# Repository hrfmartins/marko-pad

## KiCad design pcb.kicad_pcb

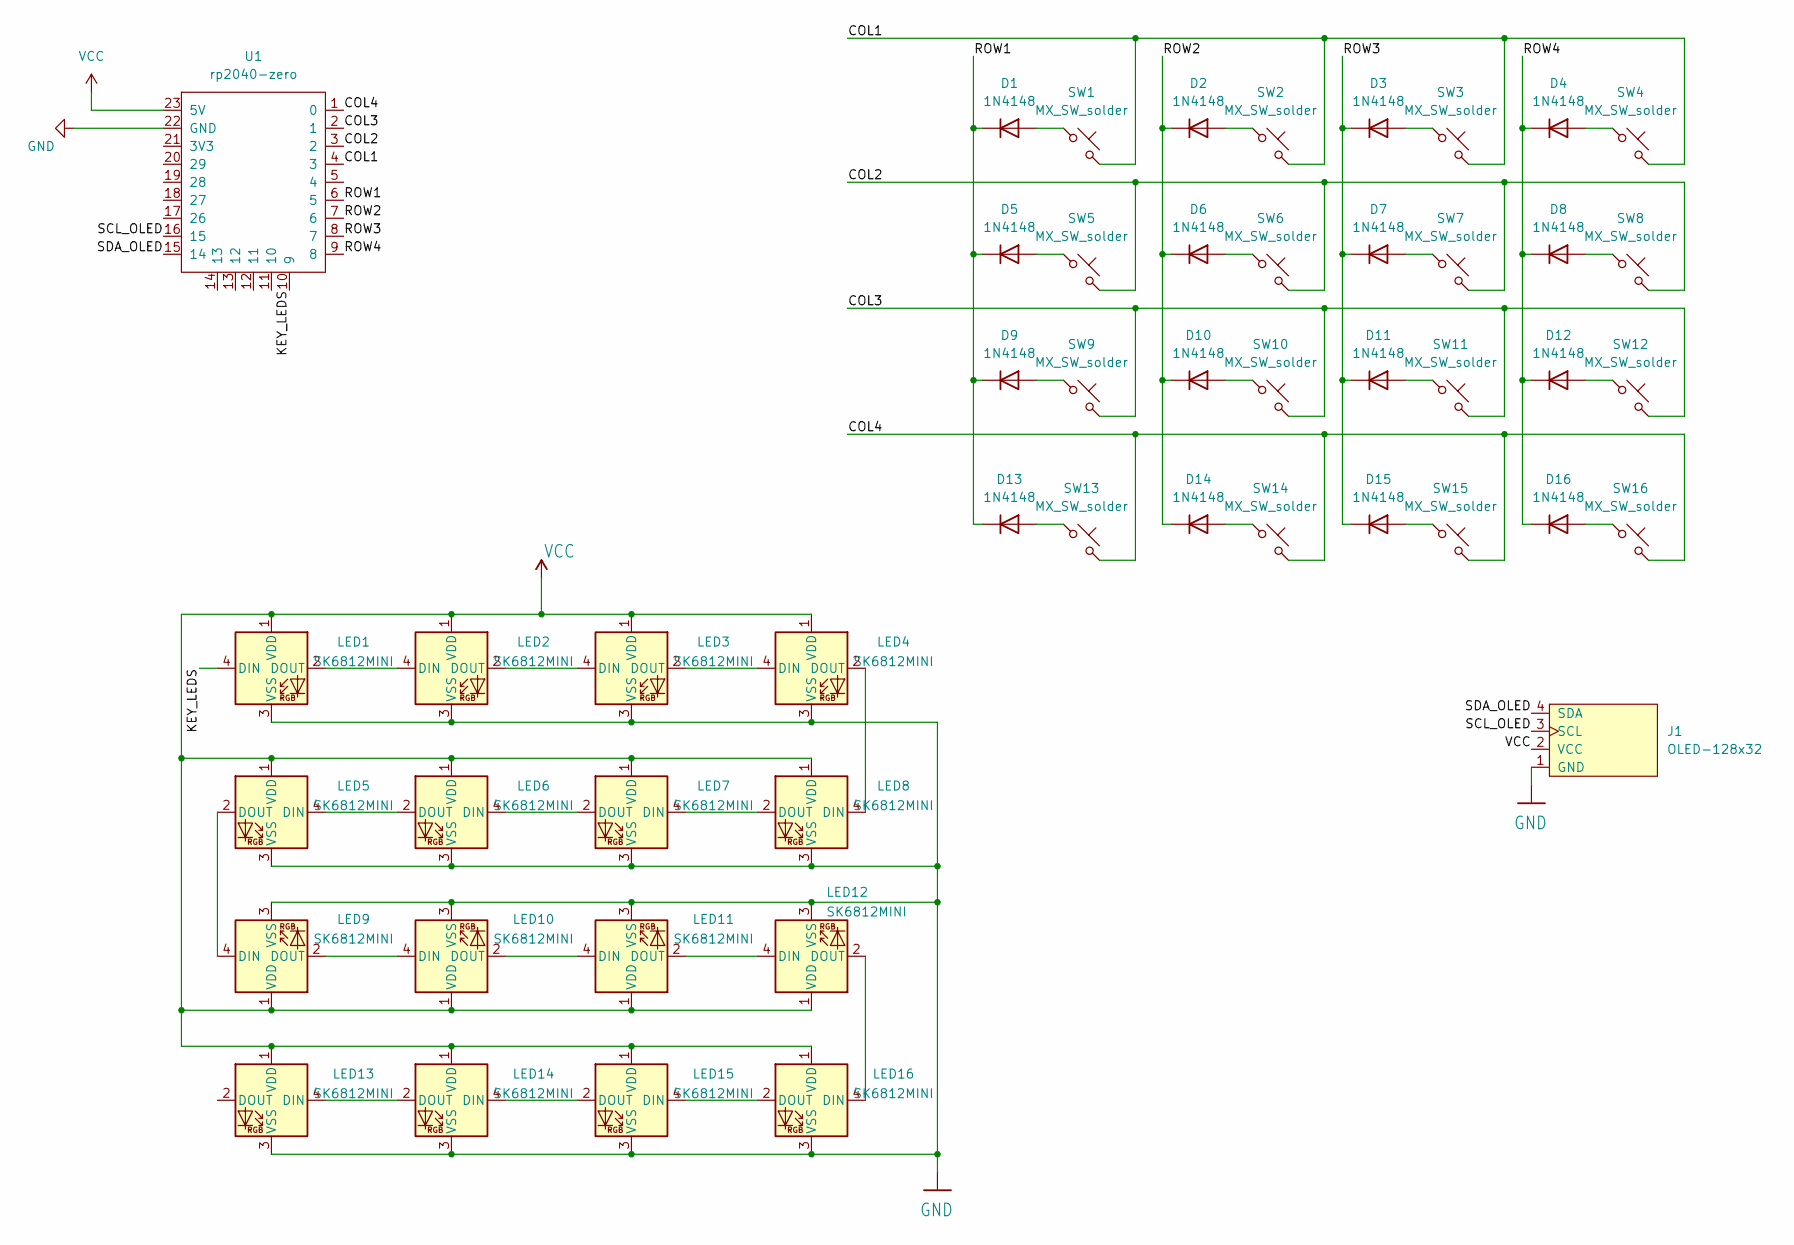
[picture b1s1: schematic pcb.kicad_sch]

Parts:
D1, D2, D3, D4, D5, D6, D7, D8, D9, D10, D11, D12, D13, D14, D15, D16: 1N4148; D_DO-35_SOD27_P7.62mm_Horizontal
J1: OLED-128x32; OLED-128x32-cutout
LED1, LED2, LED3, LED4, LED5, LED6, LED7, LED8, LED9, LED10, LED11, LED12, LED13, LED14, LED15, LED16: SK6812MINI; SK6812-MINI-E
SW1, SW2, SW3, SW4, SW5, SW6, SW7, SW8, SW9, SW10, SW11, SW12, SW13, SW14, SW15, SW16: MX_SW_solder; MXOnly-1U-Hotswap
U1: rp2040-zero; RP2040-Zero

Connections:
/COL1: SW1.2, SW2.2, SW3.2, SW4.2, U1.4 (3)
/COL2: SW5.2, SW6.2, SW7.2, SW8.2, U1.3 (2)
/COL3: SW9.2, SW10.2, SW11.2, SW12.2, U1.2 (1)
/COL4: SW13.2, SW14.2, SW15.2, SW16.2, U1.1 (0)
/KEY_LEDS: LED1.4 (DIN), U1.10 (9)
/ROW1: D1.1 (K), D5.1 (K), D9.1 (K), D13.1 (K), U1.6 (5)
/ROW2: D2.1 (K), D6.1 (K), D10.1 (K), D14.1 (K), U1.7 (6)
/ROW3: D3.1 (K), D7.1 (K), D11.1 (K), D15.1 (K), U1.8 (7)
/ROW4: D4.1 (K), D8.1 (K), D12.1 (K), D16.1 (K), U1.9 (8)
/SCL_OLED: J1.3 (SCL), U1.16 (15)
/SDA_OLED: J1.4 (SDA), U1.15 (14)
GND: J1.1 (GND), LED1.3 (VSS), LED2.3 (VSS), LED3.3 (VSS), LED4.3 (VSS), LED5.3 (VSS), LED6.3 (VSS), LED7.3 (VSS), LED8.3 (VSS), LED9.3 (VSS), LED10.3 (VSS), LED11.3 (VSS), LED12.3 (VSS), LED13.3 (VSS), LED14.3 (VSS), LED15.3 (VSS), LED16.3 (VSS), U1.22 (GND)
unnamed: D1.2 (A), SW1.1
unnamed: D2.2 (A), SW2.1
unnamed: D3.2 (A), SW3.1
unnamed: D4.2 (A), SW4.1
unnamed: D5.2 (A), SW5.1
unnamed: D6.2 (A), SW6.1
unnamed: D7.2 (A), SW7.1
unnamed: D8.2 (A), SW8.1
unnamed: D9.2 (A), SW9.1
unnamed: D10.2 (A), SW10.1
unnamed: D11.2 (A), SW11.1
unnamed: D12.2 (A), SW12.1
unnamed: D13.2 (A), SW13.1
unnamed: D14.2 (A), SW14.1
unnamed: D15.2 (A), SW15.1
unnamed: D16.2 (A), SW16.1
unnamed: LED1.2 (DOUT), LED2.4 (DIN)
unnamed: LED2.2 (DOUT), LED3.4 (DIN)
unnamed: LED3.2 (DOUT), LED4.4 (DIN)
unnamed: LED4.2 (DOUT), LED8.4 (DIN)
unnamed: LED5.4 (DIN), LED6.2 (DOUT)
unnamed: LED5.2 (DOUT), LED9.4 (DIN)
unnamed: LED6.4 (DIN), LED7.2 (DOUT)
unnamed: LED7.4 (DIN), LED8.2 (DOUT)
unnamed: LED9.2 (DOUT), LED10.4 (DIN)
unnamed: LED10.2 (DOUT), LED11.4 (DIN)
unnamed: LED11.2 (DOUT), LED12.4 (DIN)
unnamed: LED12.2 (DOUT), LED16.4 (DIN)
unnamed: LED13.4 (DIN), LED14.2 (DOUT)
unnamed: LED14.4 (DIN), LED15.2 (DOUT)
unnamed: LED15.4 (DIN), LED16.2 (DOUT)
VCC: J1.2 (VCC), LED1.1 (VDD), LED2.1 (VDD), LED3.1 (VDD), LED4.1 (VDD), LED5.1 (VDD), LED6.1 (VDD), LED7.1 (VDD), LED8.1 (VDD), LED9.1 (VDD), LED10.1 (VDD), LED11.1 (VDD), LED12.1 (VDD), LED13.1 (VDD), LED14.1 (VDD), LED15.1 (VDD), LED16.1 (VDD), U1.23 (5V)

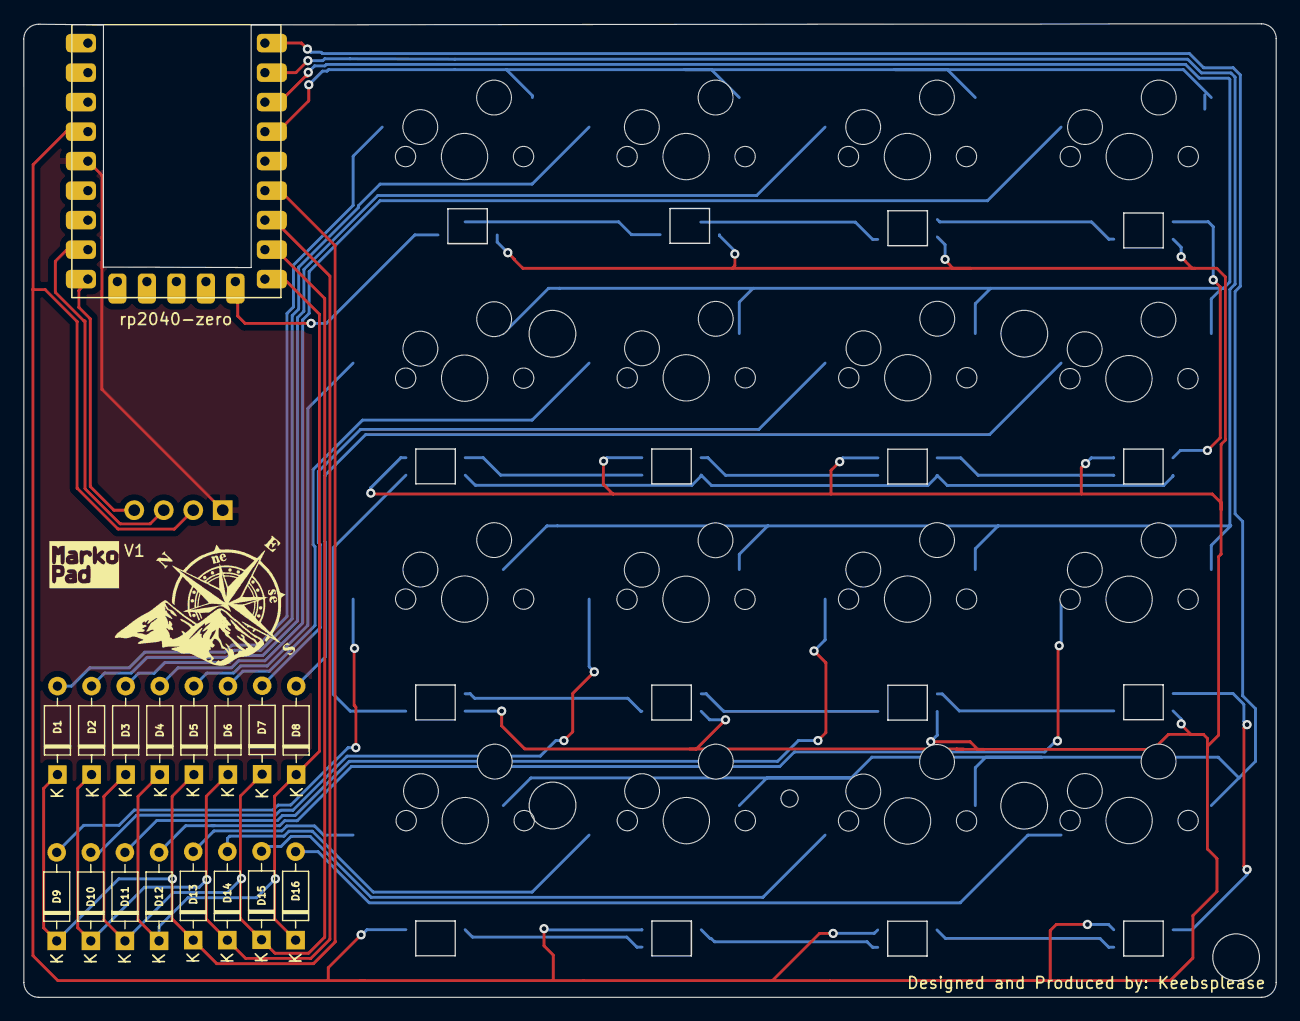
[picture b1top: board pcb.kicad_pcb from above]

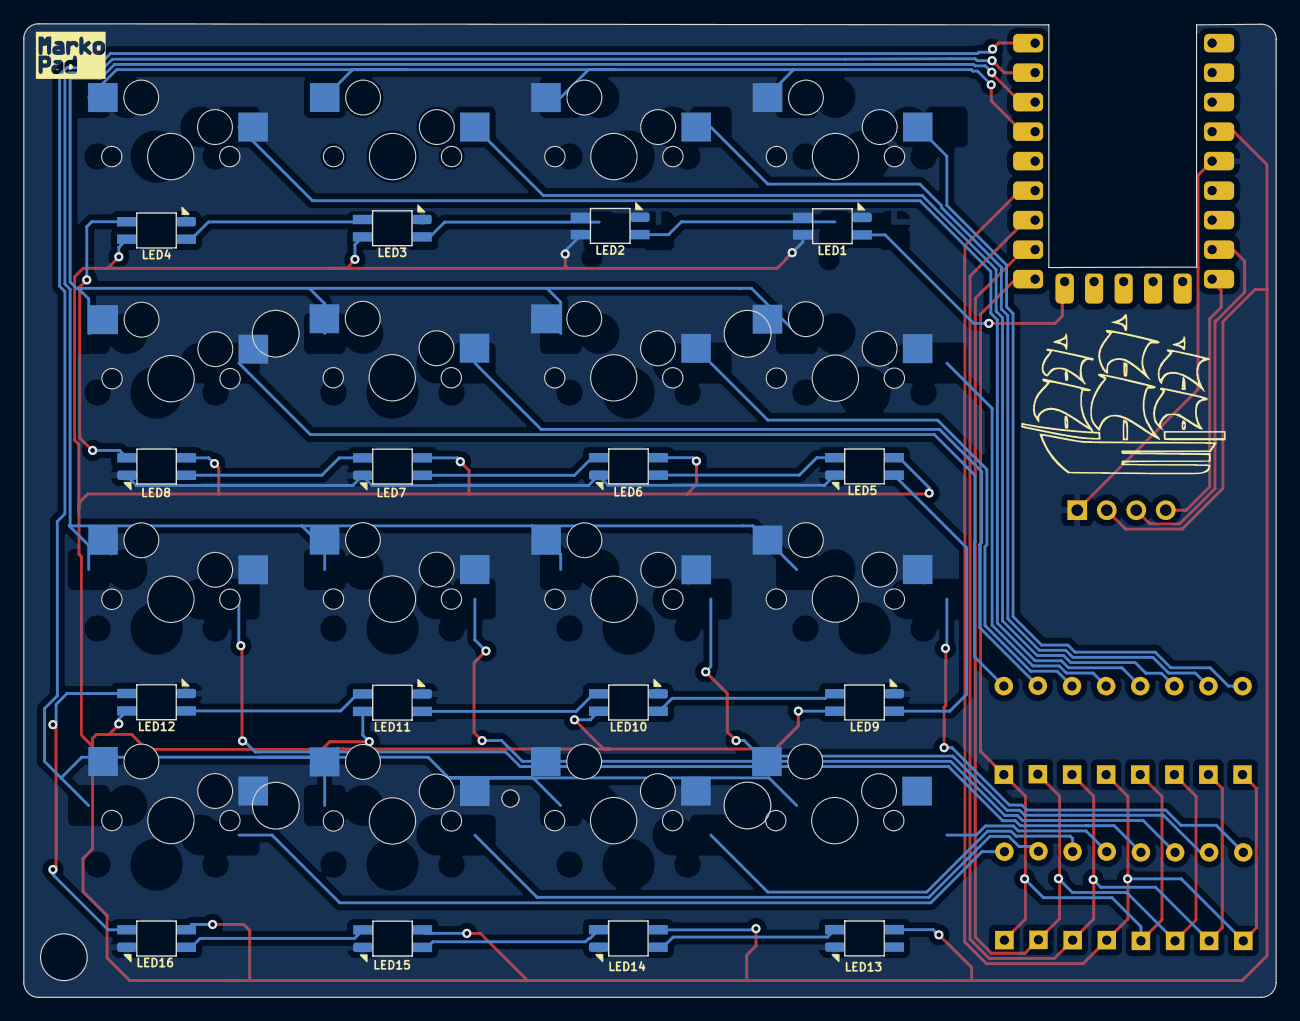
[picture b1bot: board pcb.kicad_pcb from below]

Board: 2 copper layers, 107.8 x 83.8 mm, 50 parts (16 on the bottom side), 44 nets.
